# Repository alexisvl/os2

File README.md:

# OS-2

This is my attempt at building an analog oscilloscope.

Bit of a self-indulgent project and I'm just posting it here so I don't hoard
it for myself. Nothing here is probably of use to anybody, and I have no plan
on making it in any way reproducible. License for all design files and
documentation is CC BY-NC-SA, note _non-commercial_. Any code is independently
licensed, typically GPL. If you want to spend a lot of money building something
mildly useful, feel free to build one.

## Specs

- At least 20 MHz bandwidth, maybe more
- Two to four channels
    - 1mV/div to 5V/div
    - AC, DC, GND coupling; 50 ohm or 1M termination
    - Switchable bandwidth limit per channel (if the overall bandwidth is high enough?)
- On-screen display for scale factors (raster scan)
- No software - ROM LUTs and GAL/PALs at most

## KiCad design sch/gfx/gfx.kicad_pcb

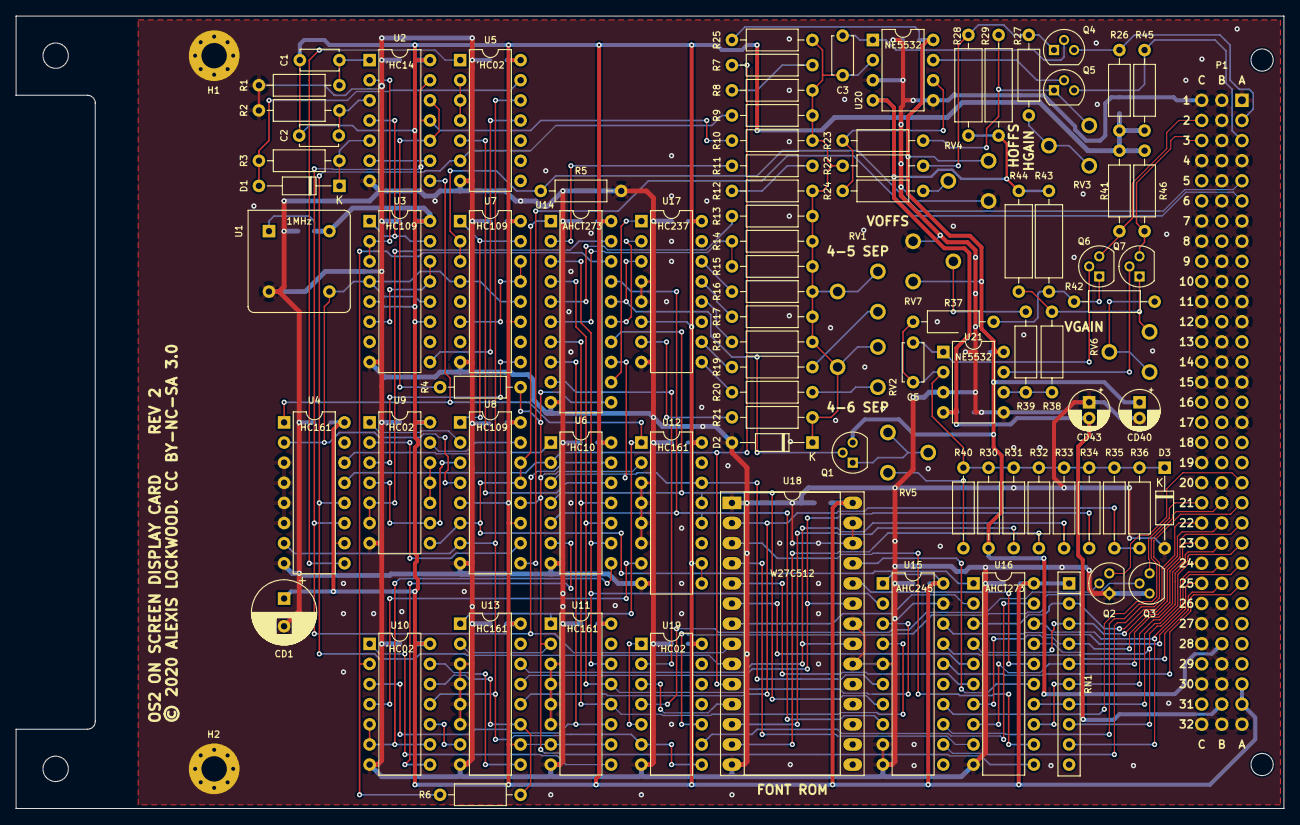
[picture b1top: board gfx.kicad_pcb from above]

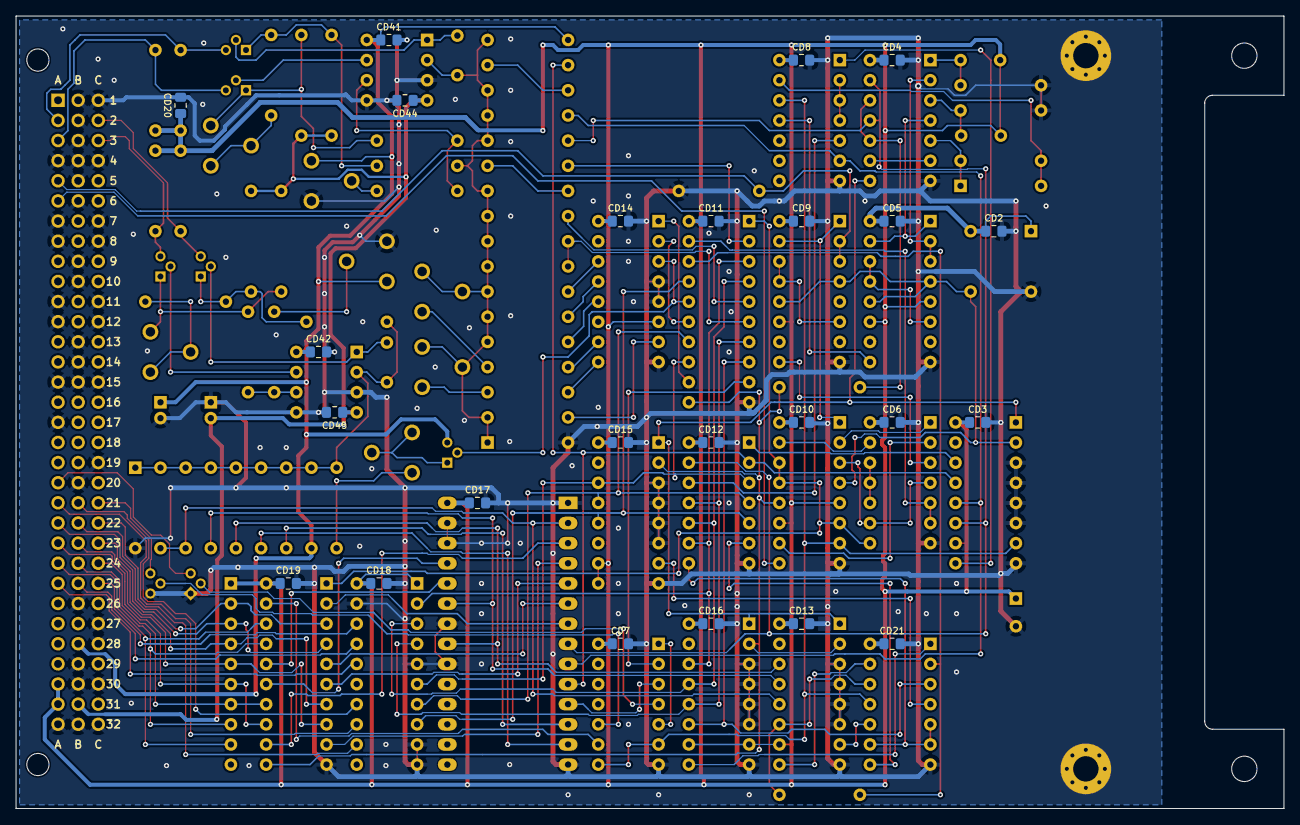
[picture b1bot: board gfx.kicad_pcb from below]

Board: 2 copper layers, 160.0 x 100.0 mm, 119 parts (24 on the bottom side), 124 nets.

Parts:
C1, C2, C3, C5: 100p; C_Disc_D4.7mm_W2.5mm_P5.00mm
CD1: 470µ; CP_Radial_D8.0mm_P3.50mm
CD2, CD3, CD4, CD5, CD6, CD7, CD8, CD9, CD10, CD11, CD12, CD13, CD14, CD15, CD16, CD17, CD18, CD19, CD20, CD21, CD41, CD42, CD44, CD45: 1µ; C_0805_2012Metric_Pad1.15x1.40mm_HandSolder
CD40, CD43: 47µ; CP_Radial_D5.0mm_P2.00mm
D1, D2, D3: 1N4148; D_DO-35_SOD27_P10.16mm_Horizontal
H1, H2: HOLE; MountingHole_3.2mm_M3_Pad_Via
P1: DIN41612_M_3x32; DIN41612_B_3x32_Horizontal
Q1, Q4, Q5, Q6, Q7: 2N3904; TO-92
Q2, Q3: 2N7000; TO-92
R1: 82k; R_Axial_DIN0207_L6.3mm_D2.5mm_P10.16mm_Horizontal
R2: 22k; R_Axial_DIN0207_L6.3mm_D2.5mm_P10.16mm_Horizontal
R3: 10k; R_Axial_DIN0207_L6.3mm_D2.5mm_P10.16mm_Horizontal
R4: 10; R_Axial_DIN0207_L6.3mm_D2.5mm_P10.16mm_Horizontal
R5: 6k8; R_Axial_DIN0207_L6.3mm_D2.5mm_P10.16mm_Horizontal
R6: 3k3; R_Axial_DIN0207_L6.3mm_D2.5mm_P10.16mm_Horizontal
R7, R8, R9, R31, R33: 499k; R_Axial_DIN0207_L6.3mm_D2.5mm_P10.16mm_Horizontal
R10, R32, R34, R35, R36: 249k; R_Axial_DIN0207_L6.3mm_D2.5mm_P10.16mm_Horizontal
R11, R12, R13, R14, R15: 68k; R_Axial_DIN0207_L6.3mm_D2.5mm_P10.16mm_Horizontal
R16: 15k; R_Axial_DIN0207_L6.3mm_D2.5mm_P10.16mm_Horizontal
R17, R24: 7k5; R_Axial_DIN0207_L6.3mm_D2.5mm_P10.16mm_Horizontal
R18, R21: 4k99; R_Axial_DIN0207_L6.3mm_D2.5mm_P10.16mm_Horizontal
R19: 18k; R_Axial_DIN0207_L6.3mm_D2.5mm_P10.16mm_Horizontal
R20: 8k2; R_Axial_DIN0207_L6.3mm_D2.5mm_P10.16mm_Horizontal
R22, R23, R37, R38: 1k6; R_Axial_DIN0207_L6.3mm_D2.5mm_P10.16mm_Horizontal
R25, R30: 6k2; R_Axial_DIN0207_L6.3mm_D2.5mm_P10.16mm_Horizontal
R26, R41, R45, R46: 75; R_Axial_DIN0207_L6.3mm_D2.5mm_P10.16mm_Horizontal
R27, R42: 100; R_Axial_DIN0207_L6.3mm_D2.5mm_P10.16mm_Horizontal
R28, R29, R43, R44: 1k; R_Axial_DIN0309_L9.0mm_D3.2mm_P12.70mm_Horizontal
R39: 3k; R_Axial_DIN0207_L6.3mm_D2.5mm_P10.16mm_Horizontal
R40: 820; R_Axial_DIN0207_L6.3mm_D2.5mm_P10.16mm_Horizontal
RN1: 1k; R_Array_SIP10
RV1, RV2: 5k; stock_pot
RV3, RV6: 50; stock_pot
RV4: 20k; stock_pot
RV5, RV7: 10k; stock_pot
U1: 1MHz; Oscillator_DIP-8
U2: 'HC14; DIP-14_W7.62mm
U3, U7, U8: 'HC109; DIP-16_W7.62mm
U4, U11, U12, U13: 'HC161; DIP-16_W7.62mm
U5, U9, U10, U19: 'HC02; DIP-14_W7.62mm
U6: 'HC10; DIP-14_W7.62mm
U14, U16: 'AHCT273; DIP-20_W7.62mm
U15: 'AHC245; DIP-20_W7.62mm
U17: 'HC237; DIP-16_W7.62mm
U18: W27C512; DIP-28_W15.24mm_Socket_LongPads
U20, U21: NE5532; DIP-8_W7.62mm

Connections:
+15V: CD40.1, CD41.1, CD42.1, P1.B28, Q1.3 (C), R25.2, R30.2, RV4.3, RV7.3, U20.8 (V+), U21.8 (V+)
-15V: CD43.2, CD44.1, CD45.1, P1.B31, R28.1, R29.1, R43.1, R44.1, U20.4 (V-), U21.4 (V-)
/CHAR0: U16.2 (Q0), U18.7 (A3)
/CHAR1: U16.5 (Q1), U18.6 (A4)
/CHAR2: U16.6 (Q2), U18.5 (A5)
/CHAR3: U16.9 (Q3), U18.4 (A6)
/CHAR4: U16.12 (Q4), U18.3 (A7)
/CHAR5: U16.15 (Q5), U18.25 (A8)
/CHAR6: U16.16 (Q6), U18.24 (A9)
/DESCENDER0: R31.2, U18.12 (D1)
/DESCENDER1: R32.2, U18.13 (D2)
/DONE#: U8.10 (Q), U9.2
/DONEREQ: U9.5, U9.6, U14.19 (Q7)
/FLD0: U14.12 (Q4), U17.1 (A0)
/FLD1: U14.15 (Q5), U17.2 (A1)
/FLD2: Q1.2 (B), U14.16 (Q6), U17.3 (A2)
/FLDREQ0: U6.3, U12.14 (Q0), U14.13 (D4), U15.6 (A4)
/FLDREQ1: U6.4, U12.13 (Q1), U14.14 (D5), U15.7 (A5)
/FLDREQ2: U6.5, U12.12 (Q2), U14.17 (D6), U15.8 (A6)
/HDOT0: R7.2, U4.13 (Q1), U6.2, U18.10 (A0)
/HDOT1: R9.2, U4.12 (Q2), U5.6, U18.9 (A1)
/HDOT2: R10.2, U2.11, U2.13, U4.11 (Q3), U6.13, U18.8 (A2)
/INTEN#: U16.19 (Q7), U19.9
/INTERFIELD_BLANK: U14.9 (Q3), U19.2
/LASTDOT: U4.9 (~Pe), U5.1
/LASTFLD#: U6.6, U10.8
/LASTPOS#: U6.8, U10.5, U10.6, U10.9
/LINE0: R33.2, U13.14 (Q0), U18.21 (A10)
/LINE1: R34.2, U13.13 (Q1), U18.23 (A11)
/LINE2: R35.2, R36.2, U13.12 (Q2), U18.2 (A12)
/PIX_BLANK: U18.11 (D0), U19.3
/POS0: R11.2, U14.2 (Q0)
/POS1: R13.2, U14.5 (Q1)
/POS2: R14.2, R15.2, U14.6 (Q2)
/POSREQ0: U6.9, U11.14 (Q0), U14.3 (D0), U15.2 (A0)
/POSREQ1: U6.10, U11.13 (Q1), U14.4 (D1), U15.3 (A1)
/POSREQ2: U6.11, U11.12 (Q2), U14.7 (D2), U15.4 (A2)
/PREBLANK: U10.3, U11.11 (Q3), U14.8 (D3)
/PREDONE: R6.2, U10.12, U13.11 (Q3)
/PREDONE': R6.1, U10.2, U14.18 (D7)
/~POR: U7.1 (R), U7.15 (R), U8.1 (R)
A2: P1.A2, Q4.3 (C), R26.1
A3: P1.A3, Q5.3 (C), R45.2
A5: P1.A5, R5.2, U7.2 (J), U7.3 (K)
A6: P1.A6, U8.9 (Q)
A20: P1.A20, Q2.3 (D)
A21: P1.A21, U15.13 (B5)
A22: P1.A22, RN1.3 (R2), U16.4 (D1)
A23: P1.A23, RN1.6 (R5), U16.13 (D4)
A24: P1.A24, RN1.9 (R8), U16.18 (D7)
A25: P1.A25, U15.16 (B2)
B21: P1.B21, U15.14 (B4)
B22: P1.B22, RN1.2 (R1), U16.3 (D0)
B23: P1.B23, RN1.5 (R4), U16.8 (D3)
B24: P1.B24, RN1.8 (R7), U16.17 (D6)
B25: P1.B25, U15.17 (B1)
C2: P1.C2, Q6.3 (C), R41.1
C3: P1.C3, Q7.3 (C), R46.2
C21: P1.C21, Q3.3 (D)
C22: P1.C22, U15.12 (B6)
C23: P1.C23, RN1.4 (R3), U16.7 (D2)
C24: P1.C24, RN1.7 (R6), U16.14 (D5)
C25: P1.C25, U15.18 (B0)
CLK: U1.5 (OUT), U3.4 (C), U3.12 (C), U4.2 (CK), U7.4 (C), U7.12 (C), U8.4 (C)
GND: CD1.2, CD2.2, CD3.2, CD4.2, CD5.2, CD6.2, CD7.2, CD8.2, CD9.2, CD10.2, CD11.2, CD12.2, CD13.2, CD14.2, CD15.2, CD16.2, CD17.2, CD18.2, CD19.2, CD20.2, CD21.2, CD40.2, CD41.2, CD42.2, CD43.1, CD44.2, CD45.2, D2.2 (A), D3.2 (A), H1.1, H2.1, P1.A1, P1.A4, P1.A7, P1.A8, P1.A11, P1.A12, P1.A15, P1.A17, P1.A32, P1.B1, P1.B2, P1.B3, P1.B4, P1.B5, P1.B6, P1.B9, P1.B10, P1.B13, P1.B14, P1.B15, P1.B20, P1.B26, P1.B29, P1.B30, P1.B32, P1.C1, P1.C4, P1.C7, P1.C8, P1.C11, P1.C12, P1.C15, P1.C19, P1.C27, P1.C28, P1.C30, P1.C32, Q2.1 (S), Q3.1 (S), R1.2, R2.2, R5.1, RV4.1, RV7.1, U1.4 (GND), U2.7 (GND), U3.8 (GND), U4.3 (P0), U4.4 (P1), U4.5 (P2), U4.6 (P3), U4.8 (GND), U5.7 (GND), U6.7 (GND), U7.8 (GND), U8.8 (GND), U9.7 (GND), U10.7 (GND), U11.3 (P0), U11.4 (P1), U11.5 (P2), U11.6 (P3), U11.8 (GND), U12.3 (P0), U12.4 (P1), U12.5 (P2), U12.6 (P3), U12.8 (GND), U13.3 (P0), U13.4 (P1), U13.5 (P2), U13.6 (P3), U13.8 (GND), U14.10 (GND), U15.5 (A3), U15.9 (A7), U15.10 (GND), U15.19 (CE), U16.10 (GND), U17.4 (~LE), U17.5 (~E1), U17.8 (GND), U18.1 (A15), U18.14 (GND), U18.20 (~CE), U18.22 (~OE), U18.26 (A13), U18.27 (A14), U19.7 (GND), U20.3 (+), U20.5 (+), U21.3 (+), U21.5 (+)
unnamed: C1.2, R1.1, U2.1
unnamed: C2.2, R2.1, U2.3
unnamed: C3.1, D2.1 (K), R8.1, R9.1, R10.1, R12.1, R13.1, R14.1, R15.1, R16.1, R17.1, R18.1, R21.1, R22.1, R25.1, RV1.2, RV1.3, RV2.2, RV2.3, U20.2 (-)
unnamed: C3.2, Q4.2 (B), U20.1
unnamed: C5.1, D3.1 (K), R30.1, R31.1, R32.1, R33.1, R34.1, R35.1, R36.1, R37.1, R40.1, U21.2 (-)
unnamed: C5.2, Q6.2 (B), U21.1
unnamed: D1.1 (K), R3.2, U2.5
unnamed: D1.2 (A), R3.1, U5.13
unnamed: Q1.1 (E), RV5.1, RV5.2
unnamed: Q2.2 (G), U19.4
unnamed: Q3.2 (G), U19.10
unnamed: Q4.1 (E), R22.2, R27.1, R28.2
unnamed: Q5.1 (E), R23.1, R29.2, RV3.3
unnamed: Q5.2 (B), U20.7
unnamed: Q6.1 (E), R37.2, R42.1, R43.2
unnamed: Q7.1 (E), R38.1, R44.2, RV6.3
unnamed: Q7.2 (B), U21.7
unnamed: R4.1, U2.10, U2.12
unnamed: R7.1, R8.2
unnamed: R11.1, R12.2
unnamed: R16.2, U17.14 (Y1)
unnamed: R17.2, U17.13 (Y2)
unnamed: R18.2, U17.12 (Y3)
unnamed: R19.1, RV1.1
unnamed: R19.2, U17.10 (Y5)
unnamed: R20.1, RV2.1
unnamed: R20.2, U17.9 (Y6)
unnamed: R21.2, U17.7 (Y7)
unnamed: R23.2, R24.1, U20.6 (-)
unnamed: R24.2, RV4.2
unnamed: R27.2, RV3.1, RV3.2
unnamed: R38.2, R39.1, U21.6 (-)
unnamed: R39.2, RV7.2
unnamed: R40.2, RV5.3
unnamed: R42.2, RV6.1, RV6.2
unnamed: U2.2, U3.2 (J), U3.3 (K)
unnamed: U2.4, U3.1 (R), U3.15 (R)
unnamed: U2.6, U2.9
unnamed: U3.6 (Q), U3.13 (K), U3.14 (J)
unnamed: U4.14 (Q0), U6.1
unnamed: U5.2, U5.3, U5.4
unnamed: U5.5, U6.12
unnamed: U7.9 (Q), U9.3
unnamed: U7.6 (Q), U7.13 (K), U7.14 (J)
unnamed: U8.2 (J), U9.1
unnamed: U8.3 (K), U9.4, U9.9
unnamed: U8.15 (R), U9.13
unnamed: U9.10, U9.11, U9.12
unnamed: U10.1, U11.9 (~Pe)
unnamed: U10.4, U12.7 (ENP)
unnamed: U10.10, U13.7 (ENP)
unnamed: U10.13, U13.9 (~Pe)
unnamed: U19.1, U19.5
POR: U3.9 (Q), U5.11
POSCLK: R4.2, U8.12 (C), U11.2 (CK), U12.2 (CK), U13.2 (CK), U14.11 (Cp), U16.11 (Cp)
RST#: U2.8, U4.1 (~MR), U11.1 (~MR), U12.1 (~MR), U13.1 (~MR)
RUN: U8.6 (Q), U8.13 (K), U8.14 (J), U9.8, U14.1 (~Mr), U16.1 (~Mr)
RUN#: U4.7 (ENP), U5.12, U8.7 (Q), U10.11, U19.6, U19.8
VCC: C1.1, C2.1, CD1.1, CD2.1, CD3.1, CD4.1, CD5.1, CD6.1, CD7.1, CD8.1, CD9.1, CD10.1, CD11.1, CD12.1, CD13.1, CD14.1, CD15.1, CD16.1, CD17.1, CD18.1, CD19.1, CD20.1, CD21.1, P1.A30, P1.A31, R26.2, R41.2, R45.1, R46.1, RN1.1 (common), U1.1 (EN), U1.8 (Vcc), U2.14 (VCC), U3.5 (S), U3.11 (S), U3.16 (VCC), U4.10 (ENT), U4.16 (VCC), U5.14 (VCC), U6.14 (VCC), U7.11 (S), U7.16 (VCC), U8.5 (S), U8.11 (S), U8.16 (VCC), U9.14 (VCC), U10.14 (VCC), U11.7 (ENP), U11.10 (ENT), U11.16 (VCC), U12.9 (~Pe), U12.10 (ENT), U12.16 (VCC), U13.10 (ENT), U13.16 (VCC), U14.20 (VCC), U15.1 (A->B), U15.20 (VCC), U16.20 (VCC), U17.6 (E2), U17.16 (VCC), U18.28 (VCC), U19.14 (VCC)

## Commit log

2020-04-25 Initial commit, add license
2020-04-25 Add docs
2020-04-29 Add some interface and protoboard stuff
2020-04-29 Add more units to charset
2020-05-05 commit some work, soz for shit commit msgs
2020-05-08 schematic cleanups
2020-05-14 Work in progress, not well organized, sorry
2020-05-14 what is happening
2020-05-24 blah blah
2020-06-30 gfx board, pcb version
2020-07-04 gfx: sch adjustments and 3d models
2020-07-04 flesh out eeplut
2020-07-05 readme update

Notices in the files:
sch/gfx/gfx.kicad_pcb:
© 2020 ALEXIS LOCKWOOD. CC BY-NC-SA 3.0
